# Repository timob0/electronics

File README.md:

# electronics
Self Designed KICad projects

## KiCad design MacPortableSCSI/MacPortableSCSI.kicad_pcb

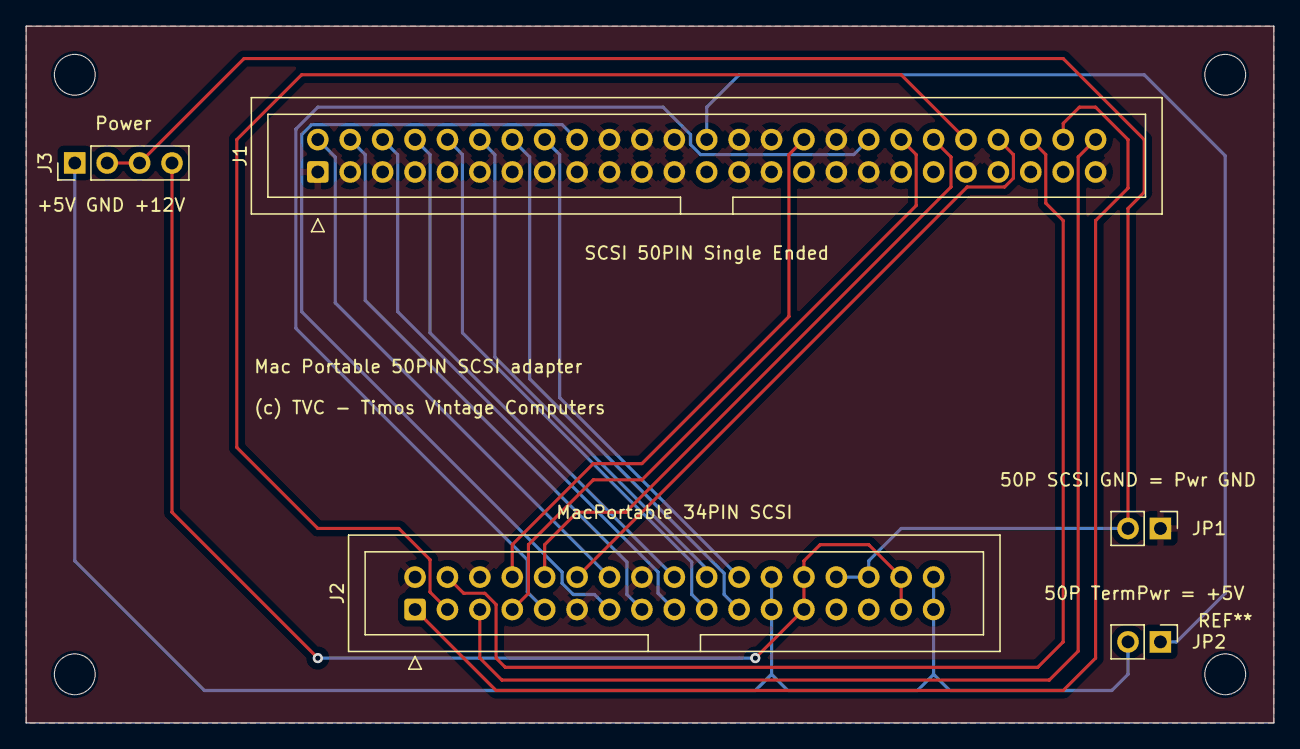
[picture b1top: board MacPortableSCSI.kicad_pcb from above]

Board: 2 copper layers, 97.8 x 54.6 mm, 5 parts (0 on the bottom side), 24 nets.

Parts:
J1: SCSI 50PIN Single Ended; IDC-Header_2x25_P2.54mm_Vertical
J2: MacPortable 34PIN SCSI; IDC-Header_2x17_P2.54mm_Vertical
J3: Power; PinHeader_1x04_P2.54mm_Vertical
JP1: 50P SCSI GND = Pwr GND; PinHeader_1x02_P2.54mm_Vertical
JP2: 50P TermPwr = +5V; PinHeader_1x02_P2.54mm_Vertical

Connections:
+5V: J2.23, J2.24, J2.33, J2.34, J3.1, JP2.2 (B)
+12V: J2.25, J2.26, J2.31, J2.32, J3.4
GND: J2.28, J2.30, J3.2, J3.3, JP1.2 (B)
GNDS: J1.1, J1.3, J1.5, J1.7, J1.9, J1.11, J1.13, J1.15, J1.17, J1.19, J1.20, J1.21, J1.22, J1.23, J1.24, J1.27, J1.28, J1.29, J1.30, J1.31, J1.33, J1.34, J1.35, J1.37, J1.39, J1.41, J1.43, J1.45, J1.47, J1.49, J2.2, J2.6, J2.11, J2.16, JP1.1 (A)
unnamed: J1.2, J2.14
unnamed: J1.4, J2.15
unnamed: J1.6, J2.17
unnamed: J1.8, J2.18
unnamed: J1.10, J2.19
unnamed: J1.12, J2.20
unnamed: J1.14, J2.21
unnamed: J1.16, J2.22
unnamed: J1.18, J2.13
unnamed: J1.26, JP2.1 (A)
unnamed: J1.32, J2.8
unnamed: J1.36, J2.9
unnamed: J1.38, J2.7
unnamed: J1.40, J2.10
unnamed: J1.42, J2.3
unnamed: J1.44, J2.12
unnamed: J1.46, J2.4
unnamed: J1.48, J2.1
unnamed: J1.50, J2.5
unnamed: J2.27, J2.29

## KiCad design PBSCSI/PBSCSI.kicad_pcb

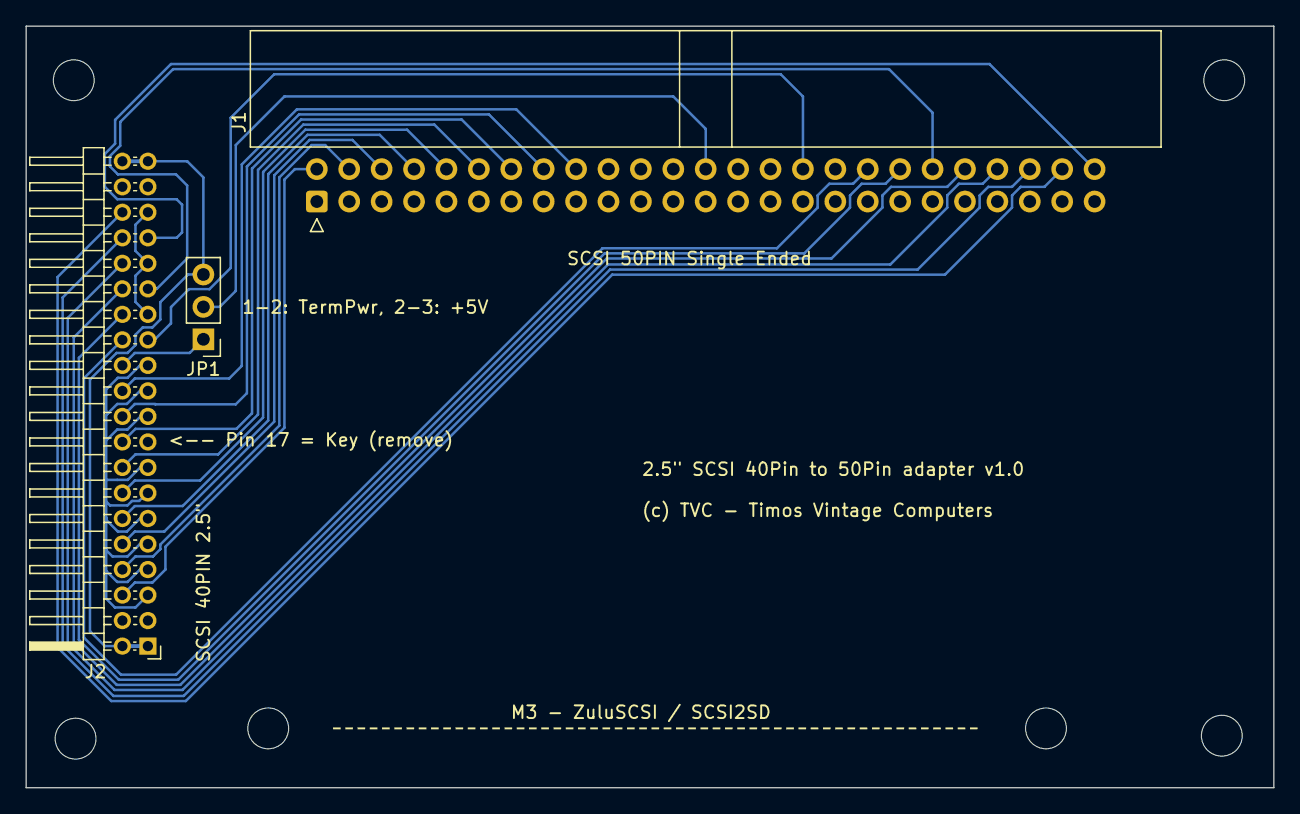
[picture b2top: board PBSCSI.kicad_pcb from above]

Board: 2 copper layers, 97.8 x 59.7 mm, 4 parts (0 on the bottom side), 22 nets.

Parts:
J1: SCSI 50PIN Single Ended; IDC-Header_2x25_P2.54mm_Horizontal
J2: SCSI 40PIN 2.5"; PinHeader_2x20_P2.00mm_Horizontal
JP1: 1-2: TermPwr, 2-3: +5V; PinHeader_1x03_P2.54mm_Vertical
M3 - ZuluSCSI / SCSI2SD: MountingHole_3.2mm_M3

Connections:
+5V: J2.1, J2.2, J2.39, J2.40, JP1.3 (B)
GND: J1.1, J1.3, J1.5, J1.7, J1.9, J1.11, J1.13, J1.15, J1.17, J1.19, J1.20, J1.21, J1.22, J1.23, J1.24, J1.27, J1.28, J1.29, J1.30, J1.31, J1.33, J1.34, J1.35, J1.37, J1.39, J1.41, J1.43, J1.45, J1.47, J1.49, J2.5, J2.7, J2.9, J2.11, J2.13, J2.15, J2.19, J2.21, J2.23, J2.27, J2.31, J2.35
unnamed: J1.2, J2.6
unnamed: J1.4, J2.8
unnamed: J1.6, J2.10
unnamed: J1.8, J2.12
unnamed: J1.10, J2.14
unnamed: J1.12, J2.16
unnamed: J1.14, J2.18
unnamed: J1.16, J2.20
unnamed: J1.18, J2.22
unnamed: J1.26, JP1.2 (C)
unnamed: J1.32, J2.25
unnamed: J1.36, J2.26
unnamed: J1.38, J2.28
unnamed: J1.40, J2.29
unnamed: J1.42, J2.30
unnamed: J1.44, J2.32
unnamed: J1.46, J2.34
unnamed: J1.48, J2.36
unnamed: J1.50, J2.33
unnamed: J2.24, JP1.1 (A)

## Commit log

2023-09-24 40pin 2.5" SCSI to regular 50pin SCSI
    This is an adapter plate to install a SCSI2SD or ZuluSCSI compact board in a Macintosh PowerBook with SCSI interface.
2023-09-24 MacPortable 34pin SCSI to regular 50pin SCSI
    This is a simple adapter to connect regular 50pin SCSI devices to the MacPortables internal 34pin bus.
    Note: untested - use at your own risk.
